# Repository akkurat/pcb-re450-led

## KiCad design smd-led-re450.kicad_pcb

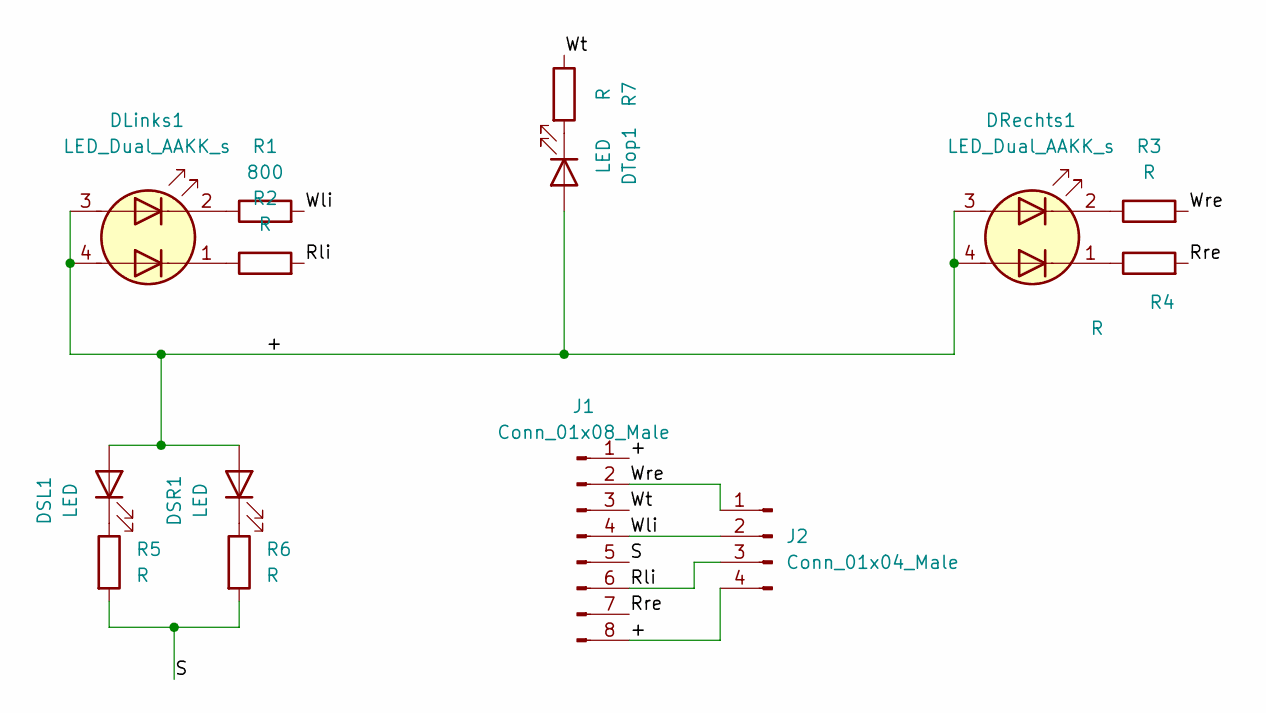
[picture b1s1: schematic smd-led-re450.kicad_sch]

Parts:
DLinks1: LED_Dual_AAKK_s; LED_0605_1613Metric
DRechts1: LED_Dual_AAKK_s; LED_0605_1613Metric
DSL1: LED; LED_1206_3216Metric_Pad1.42x1.75mm_HandSolder
DSR1: LED; LED_1206_3216Metric_Pad1.42x1.75mm_HandSolder
DTop1: LED; LED_0603_1608Metric_Pad1.05x0.95mm_HandSolder
J1: Conn_01x08_Male; PinHeader_1x08_P1.27mm_Vertical
J2: Conn_01x04_Male; PinHeader_1x04_P1.27mm_Vertical
R1: 800; R_0603_1608Metric_Pad0.98x0.95mm_HandSolder
R2, R3, R4, R5, R6, R7: R; R_0603_1608Metric_Pad0.98x0.95mm_HandSolder

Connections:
/+: DLinks1.3 (A1), DLinks1.4 (A2), DRechts1.3 (A1), DRechts1.4 (A2), DSL1.2 (A), DSR1.2 (A), DTop1.2 (A), J1.1, J1.8, J2.4
/Rli: J1.6, J2.3, R2.2
/Rre: J1.7, R4.2
/S: J1.5, R5.2, R6.2
/Wli: J1.4, J2.2, R1.2
/Wre: J1.2, J2.1, R3.2
/Wt: J1.3, R7.1
unnamed: DLinks1.1 (K2), R2.1
unnamed: DLinks1.2 (K1), R1.1
unnamed: DRechts1.1 (K2), R4.1
unnamed: DRechts1.2 (K1), R3.1
unnamed: DSL1.1 (K), R5.1
unnamed: DSR1.1 (K), R6.1
unnamed: DTop1.1 (K), R7.2

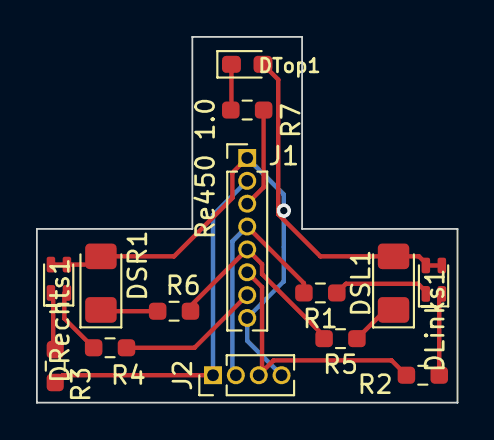
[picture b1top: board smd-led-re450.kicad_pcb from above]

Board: 2 copper layers, 23.4 x 20.3 mm, 14 parts (0 on the bottom side), 14 nets.

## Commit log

2022-03-07 LED board for Re450
2022-03-30 V1.1
2022-03-30 Before resizing
